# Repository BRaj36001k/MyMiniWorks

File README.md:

# Boost-Converter

A collection of mini projects in hardware design, PCB layout, simulation, and coding.

## Projects

### Boost Converter
A PCB design for a boost converter circuit built using KiCad.
- **Tool:** KiCad
- **Status:** Completed
- **Files:** `boost-converter/`

## Tools Used
- KiCad (PCB Design)

## Author
B-Raj15 — [GitHub](https://github.com/BRaj36001k)

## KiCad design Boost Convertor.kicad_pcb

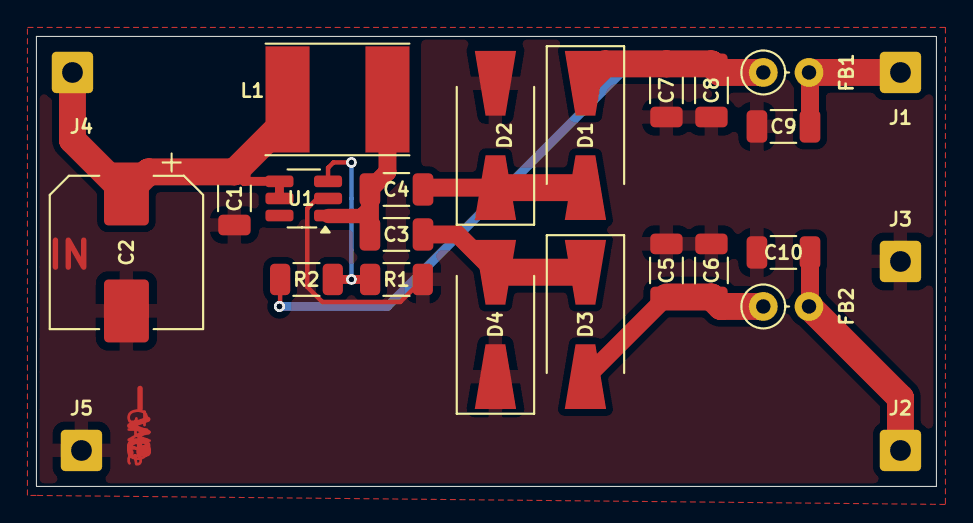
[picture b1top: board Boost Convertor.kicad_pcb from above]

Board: 2 copper layers, 50.0 x 25.0 mm, 25 parts (0 on the bottom side), 10 nets.

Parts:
C1: 100n; C_1206_3216Metric
C2: 220uF/16v; CP_Elec_8x10
C3, C4, C5, C6, C7, C8, C9, C10: 10u; C_1206_3216Metric
D1, D2, D3, D4: SS34; D_SMA-SMB_Universal_Handsoldering
FB1, FB2: FB; L_Axial_L5.3mm_D2.2mm_P2.54mm_Vertical_Vishay_IM-1
J1: V+(OUT); SolderWire-0.5sqmm_1x01_D0.9mm_OD2.3mm
J2: V-(OUT); SolderWire-0.5sqmm_1x01_D0.9mm_OD2.3mm
J3: GND(OUT); SolderWire-0.5sqmm_1x01_D0.9mm_OD2.3mm
J4: V+(IN); SolderWire-0.5sqmm_1x01_D0.9mm_OD2.3mm
J5: GND(IN); SolderWire-0.5sqmm_1x01_D0.9mm_OD2.3mm
L1: L_Ferrite; L_Taiyo-Yuden_NR-60xx_HandSoldering
R1, R2: R; R_1206_3216Metric
U1: MT3608; SOT-23-6_Handsoldering

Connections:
GND: C1.2, C2.2, C5.1, C6.1, C7.2, C8.2, C9.2, C10.2, D2.2 (A), D4.1 (K), J3.1, J5.1, R1.1, U1.2 (GND)
unnamed: C4.2, D1.2 (A), D2.1 (K)
unnamed: C7.1, C8.1, D1.1 (K), FB1.1, R2.2
unnamed: C5.2, C6.2, D3.2 (A), FB2.1
unnamed: C3.2, D3.1 (K), D4.2 (A)
unnamed: C9.1, FB1.2, J1.1
unnamed: C10.1, FB2.2, J2.1
unnamed: C1.1, C2.1, J4.1, L1.1, U1.4 (EN), U1.5 (IN)
unnamed: R1.2, R2.1, U1.3 (FB)
unnamed: C3.1, C4.1, L1.2, U1.1 (SW)

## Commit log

2026-06-15 Add files via upload
    MT3608 Switching Regulator IC based DC-DC Boost Convert designed (using KiCad10.0)
2026-06-18 Rename Boost Convertor Schematic.png to Boost-Convertor-Schematic.png
2026-06-18 Rename Boost Convertor.kicad_pro to Boost-Convertor.kicad_pro
2026-06-18 Rename Boost Convertor.kicad_pcb to Boost-Convertor.kicad_pcb
2026-06-18 Update README with project descriptions and author
    Expanded project details and added author information.
